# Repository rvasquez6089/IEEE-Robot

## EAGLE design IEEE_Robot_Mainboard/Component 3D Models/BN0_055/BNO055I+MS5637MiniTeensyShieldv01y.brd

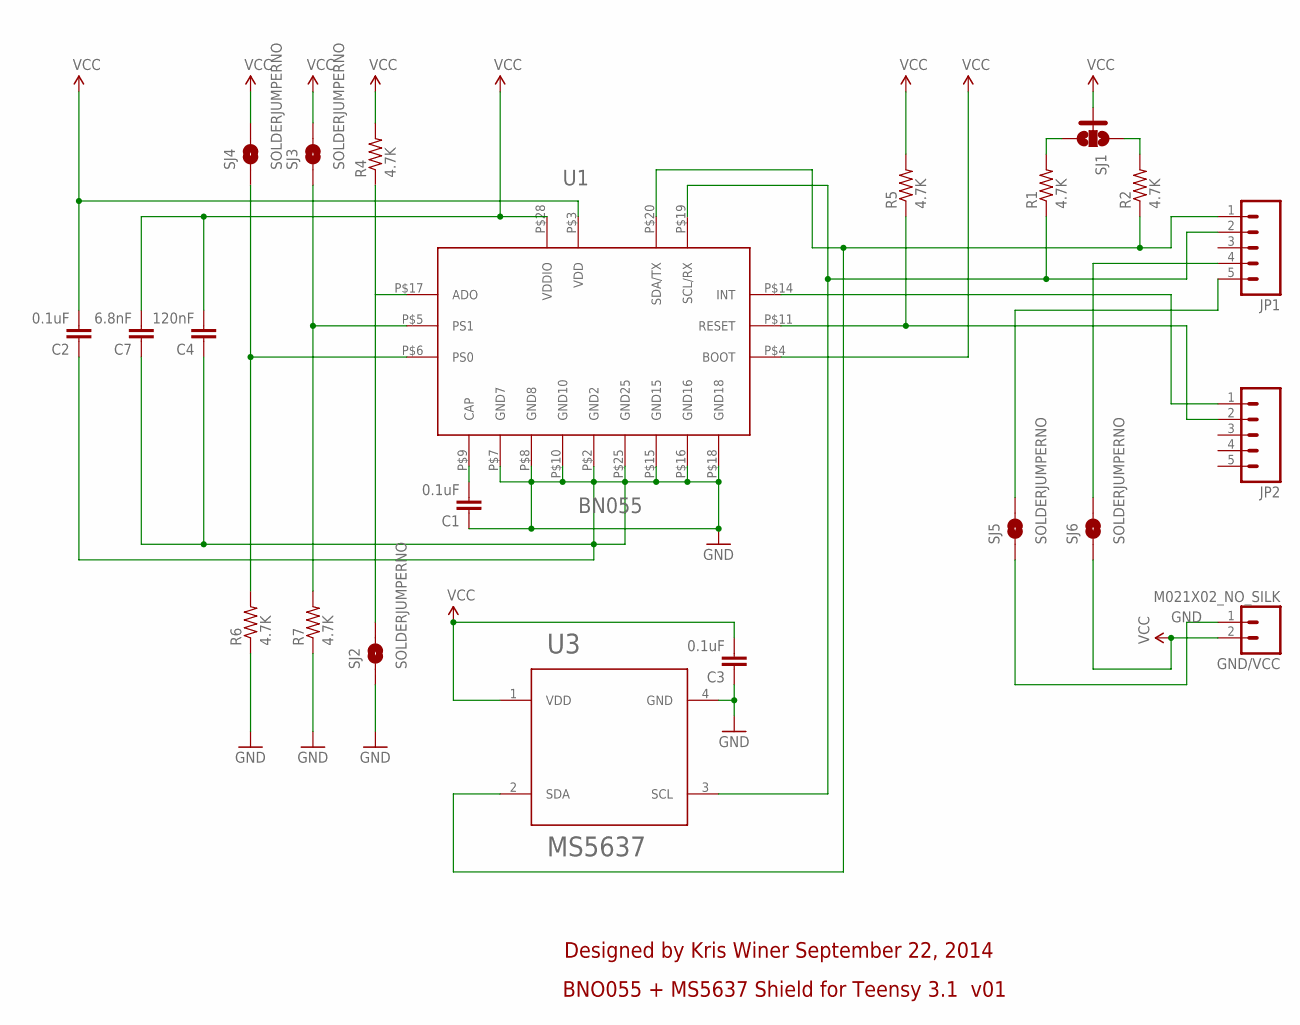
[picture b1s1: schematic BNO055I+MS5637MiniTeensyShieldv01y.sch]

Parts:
C1, C2, C3: 0.1uF; 0603-CAP
C4: 120nF; 0603-CAP
C7: 6.8nF; 0603-CAP
GND/VCC: M021X02_NO_SILK; 1X02_NO_SILK
JP1, JP2: M05NO_SILK; 1X05_NO_SILK
R1, R2, R4, R5, R6, R7: 4.7K; 0603-RES
SJ1: SOLDERJUMPER_2WAYS; SJ_3
SJ2, SJ3, SJ4, SJ5, SJ6: SOLDERJUMPERNO; SJ_2S-NO
U1: BN055; LGA28
U3: MS5637; MS5637QFN-4

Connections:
GND: C1.1, C2.1, C3.1, C4.1, C7.1, GND/VCC.1, R6.1, R7.1, SJ2.1, SJ5.1, U1.P$2 (GND2), U1.P$7 (GND7), U1.P$8 (GND8), U1.P$10 (GND10), U1.P$15 (GND15), U1.P$16 (GND16), U1.P$18 (GND18), U1.P$25 (GND25), U3.4 (GND)
unnamed: JP2.1, U1.P$14 (INT)
unnamed: JP2.2, R5.1, U1.P$11 (RESET)
unnamed: C1.2, U1.P$9 (CAP)
unnamed: R4.1, SJ2.2, U1.P$17 (ADO)
unnamed: R7.2, SJ3.1, U1.P$5 (PS1)
unnamed: JP1.4, SJ6.2
unnamed: R1.2, SJ1.3
unnamed: R2.2, SJ1.1
unnamed: JP1.5, SJ5.2
unnamed: R6.2, SJ4.1, U1.P$6 (PS0)
SCL: JP1.2, R1.1, U1.P$19 (SCL/RX), U3.3 (SCL)
SDA: JP1.1, R2.1, U1.P$20 (SDA/TX), U3.2 (SDA)
VCC: C2.2, C3.2, C4.2, C7.2, GND/VCC.2, R4.2, R5.2, SJ1.2, SJ3.2, SJ4.2, SJ6.1, U1.P$3 (VDD), U1.P$4 (BOOT), U1.P$28 (VDDIO), U3.1 (VDD)

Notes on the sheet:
Designed by Kris Winer September 22, 2014
BNO055 + MS5637 Shield for Teensy 3.1 v01

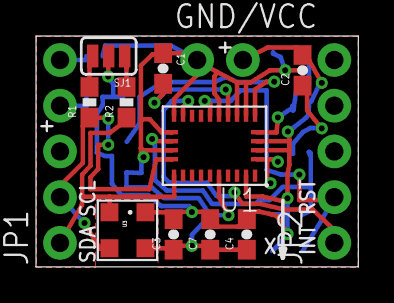
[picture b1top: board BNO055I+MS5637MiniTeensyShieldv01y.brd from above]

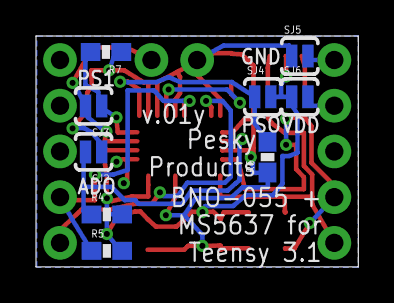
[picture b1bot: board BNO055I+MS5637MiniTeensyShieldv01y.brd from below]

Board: 2 copper layers, 17.9 x 12.8 mm, 22 parts (9 on the bottom side), 14 nets.

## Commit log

2016-02-13 :boom::camel: Added .gitattributes & .gitignore files
2016-02-14 ONline
2016-02-16 H bridge layout started
2016-02-17 Saved
2016-02-18 Completed Version of the H bridge
    The design still needs to be replicated. The board shape needs to be
    finalized.
2016-02-19 Created SolidWorks Assembly
2016-02-21 Added Multi-Channel Design Stuffs
    Also added some TI design stuffs
2016-02-22 Added Power Supply, Arduino, RPI Connector, 3.3V Reg, I2C IO Expander
2016-02-23 Started board layout, Final Schematic almost done
2016-02-23 Downloaded some models
2016-02-25 Started Board design
    Need to Ultrasonic sensor connectors and servo connectors
2016-02-28 Started Laying out Board Design~!
2016-02-28 Working on it
2016-02-28 Positioned Components!
2016-02-28 Saved and CLosed
2016-03-01 Started Board Layout
2016-03-02 Added Another Level Shifter and Updated Bom
2016-03-02 Updated Todo List
2016-03-03 Routing
2016-03-03 Routing.....
2016-03-05 Added A/D Converter and Connectors for it
2016-03-06 Almost DONE
2016-03-06 like only 38 errors BOMB
2016-03-06 Finished Board Layout!
2016-03-07 Finalizing BOM
2016-03-08 Finished Final Revisions A
2016-03-08 updated git ignore
2016-03-09 Created PDFS
2016-03-13 Started Solidworks Model
2016-03-13 refreshed
2016-03-22 built 3 model of robot
2017-09-01 Created PDF's for the teammmmm

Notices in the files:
parts and their libraries:
SparkFun-Capacitors: Licensing: CC v3.0 Share-Alike You are welcome to use this library for commercial purposes.
SparkFun-DiscreteSemi: Licensing: Creative Commons ShareAlike 4.0 International - https://creativecommons.org/licenses/by-sa/4.0
